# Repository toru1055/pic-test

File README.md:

# pic-test

## プッシュでラジオ体操
### 1. sin波で音楽再生
  - [x] オーディオアンプなし版
    - [x] 020 一定間隔でLEDを点滅させたい（MCCでタイマ設定）
    - [x] 075 MCCでオペアンプを設定して使いたい
    - [x] 101 正弦波を出力したい
  - [ ] オーディオアンプあり版

### 2. SPI通信でフラッシュメモリ読み書き
  - [x] 071 MCCでUSARTを設定して使いたい
    - [x] `$ screen /dev/tty.usbserial-0001 9600`
  - [x] 074 MCCでSPIを設定して使いたい
  - [x] 051 SPI接続の大容量フラッシュメモリを使いたい

### 3. フラッシュメモリから音声データを再生
  - [x] WAV形式のフォーマットを理解する
  - [x] `$ xxd 1164_8bit.wav | head`を見れば大体わかるが、データ部は80バイト目くらいからなので80バイトオフセットすれば良さそう
  - [x] [wav converter](https://audio.online-convert.com/convert-to-wav): 8bit モノラルの1000Hzに変換
  - [x] 104 WAVファイルをフラッシュメモリに書き込みたい
    - [x] windowsのteratermが最適。
  - [x] 103 WAVファイルの音楽を再生したい

### 4. ボタン割り込み制御：ボタンを押したら対応する音声ファイルを割り込み再生
- [x] Pin ManagerでIOC対象のPINを設定
- [x] Timer割り込みではなく、通常のDelayメソッドで音楽再生するメソッドを用意
- [x] Interrupt Handlerを実装して設定する
- [x] 1, 2番pinを押したら再生

### 5. 仕上げ
- [ ] ラジオ体操の音源を入れる
- [ ] PCBの設計

### 6. 音源をWAV形式で用意する
#### ffmpegをインストール
```
$ brew install homebrew-ffmpeg/ffmpeg/ffmpeg
```

#### mp3音源を連結する
```
$ for f in *.mp3; do echo "file '$f'" >> mylist.txt; done
$ ffmpeg -f concat -safe 0 -i mylist.txt -c copy output.mp3
```

#### MP3→WAV(8kHz,8bit,mono)へ変換
```
$ ffmpeg -i output.mp3 -ac 1 -ar 8000 -acodec pcm_u8 output.wav
```

## 音声ファイルのwifiアップロード
### 1. esp-wroom-02でアップロードされたファイルをSPI通信でフラッシュメモリ書き込み

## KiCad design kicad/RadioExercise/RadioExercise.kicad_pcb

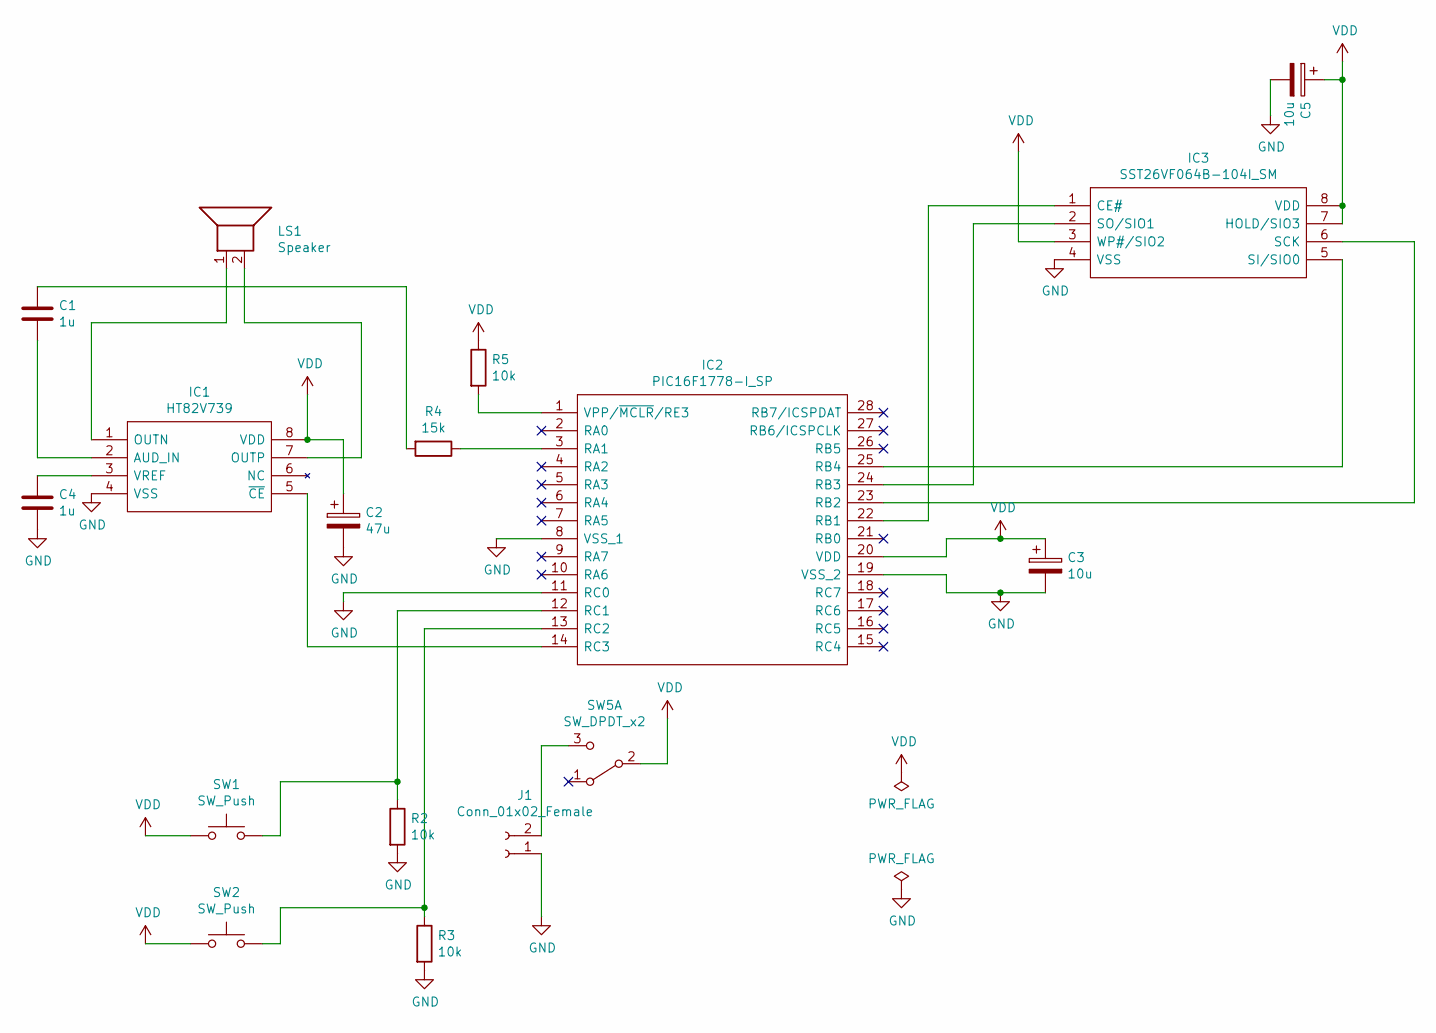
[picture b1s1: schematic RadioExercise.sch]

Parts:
C1, C4: 1u; C_Disc_D7.5mm_W5.0mm_P5.00mm
C2: 47u; CP_Radial_D4.0mm_P1.50mm
C3, C5: 10u; CP_Radial_D4.0mm_P1.50mm
IC1: HT82V739; DIP-8_W7.62mm; Manufacturer_Part_Number HT82V739
IC2: PIC16F1778-I_SP; DIP794W56P254L3486H508Q28N; Manufacturer_Part_Number PIC16F1778-I/SP; Mouser Part Number 579-PIC16F1778-I/SP
IC3: SST26VF064B-104I_SM; SOIC127P794X203-8N; Manufacturer_Part_Number SST26VF064B-104I/SM; Mouser Part Number 579-ST26VF064B104ISM
J1: Conn_01x02_Female; Conn_01x02_SMD
LS1: Speaker; Conn_01x02_SMD
R2, R3, R5: 10k; R_Axial_DIN0207_L6.3mm_D2.5mm_P7.62mm_Horizontal
R4: 15k; R_Axial_DIN0207_L6.3mm_D2.5mm_P7.62mm_Horizontal
SW1, SW2: SW_Push; SW_PUSH_6mm
SW5: SW_DPDT_x2; SW_slide_01x03_THT

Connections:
GND: C2.2, C3.2, C4.2, C5.2, IC1.4 (VSS), IC2.8 (VSS_1), IC2.11 (RC0), IC2.19 (VSS_2), IC3.4 (VSS), J1.1, R2.2, R3.2
unnamed: C1.1, R4.2
unnamed: C1.2, IC1.2 (AUD_IN)
unnamed: C4.1, IC1.3 (VREF)
unnamed: IC1.1 (OUTN), LS1.1
unnamed: IC1.5 (~CE), IC2.14 (RC3)
unnamed: IC1.7 (OUTP), LS1.2
unnamed: IC2.1 (VPP/~MCLR~/RE3), R5.2
unnamed: IC2.3 (RA1), R4.1
unnamed: IC2.12 (RC1), R2.1, SW1.2
unnamed: IC2.13 (RC2), R3.1, SW2.2
unnamed: IC2.22 (RB1), IC3.1 (CE#)
unnamed: IC2.23 (RB2), IC3.6 (SCK)
unnamed: IC2.24 (RB3), IC3.2 (SO/SIO1)
unnamed: IC2.25 (RB4), IC3.5 (SI/SIO0)
unnamed: J1.2, SW5.3 (C)
VDD: C2.1, C3.1, C5.1, IC1.8 (VDD), IC2.20 (VDD), IC3.3 (WP#/SIO2), IC3.7 (HOLD/SIO3), IC3.8 (VDD), R5.1, SW1.1, SW2.1, SW5.2 (B)

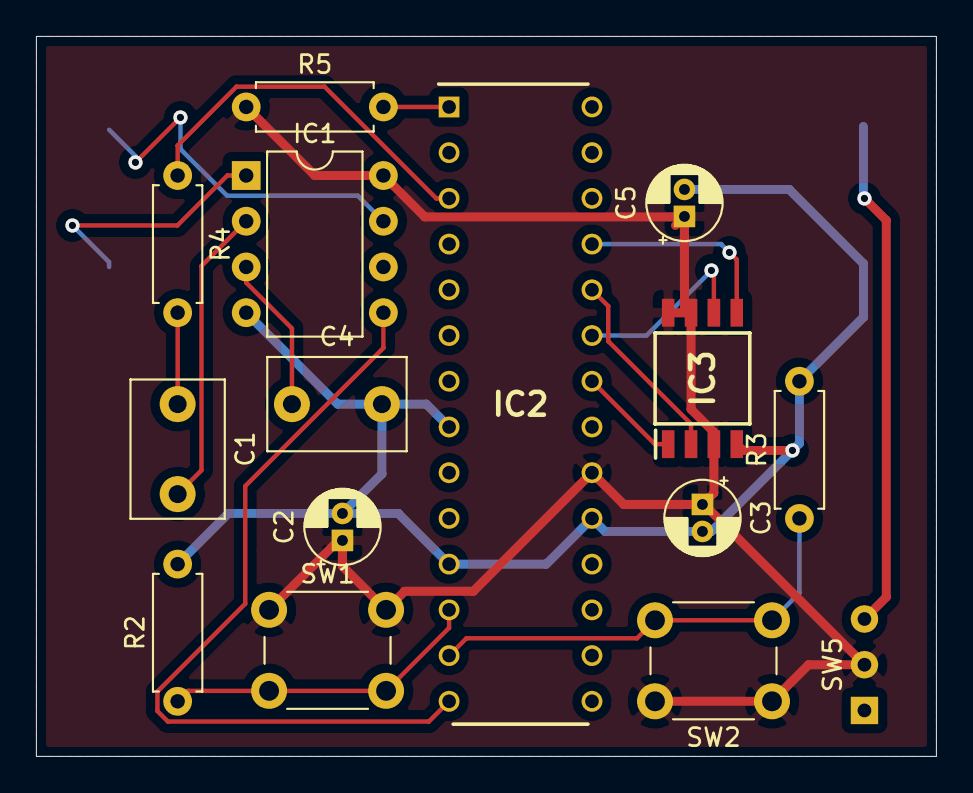
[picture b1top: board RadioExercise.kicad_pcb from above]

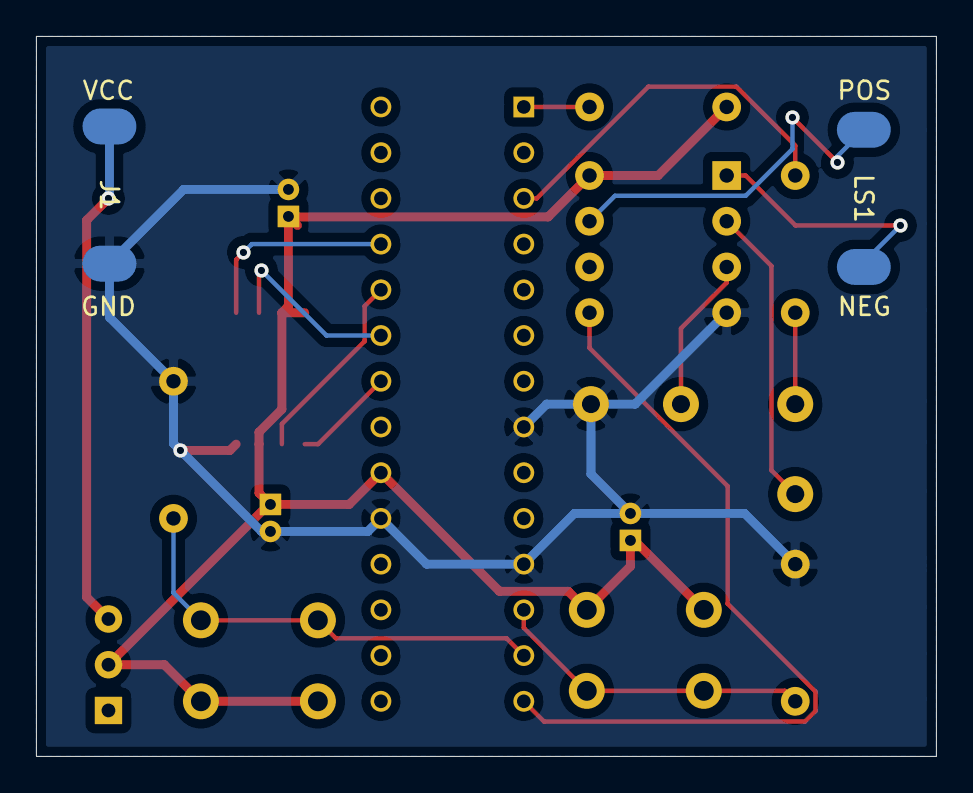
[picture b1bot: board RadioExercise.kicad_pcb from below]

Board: 2 copper layers, 50.0 x 40.0 mm, 17 parts (2 on the bottom side), 17 nets.

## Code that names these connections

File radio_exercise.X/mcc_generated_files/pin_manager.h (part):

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#define RA1_SetHigh()            do { LATAbits.LATA1 = 1; } while(0)
#define RA1_SetLow()             do { LATAbits.LATA1 = 0; } while(0)
#define RA1_Toggle()             do { LATAbits.LATA1 = ~LATAbits.LATA1; } while(0)
#define RA1_GetValue()              PORTAbits.RA1
#define RA1_SetDigitalInput()    do { TRISAbits.TRISA1 = 1; } while(0)
#define RA1_SetDigitalOutput()   do { TRISAbits.TRISA1 = 0; } while(0)
#define RA1_SetPullup()             do { WPUAbits.WPUA1 = 1; } while(0)
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// get/set IO_RB1 aliases
#define IO_RB1_TRIS                 TRISBbits.TRISB1
#define IO_RB1_LAT                  LATBbits.LATB1
#define IO_RB1_PORT                 PORTBbits.RB1
#define IO_RB1_WPU                  WPUBbits.WPUB1
#define IO_RB1_ANS                  ANSELBbits.ANSB1
#define IO_RB1_SetHigh()            do { LATBbits.LATB1 = 1; } while(0)
#define IO_RB1_SetLow()             do { LATBbits.LATB1 = 0; } while(0)
#define IO_RB1_Toggle()             do { LATBbits.LATB1 = ~LATBbits.LATB1; } while(0)
#define IO_RB1_GetValue()           PORTBbits.RB1
#define IO_RB1_SetDigitalInput()    do { TRISBbits.TRISB1 = 1; } while(0)
#define IO_RB1_SetDigitalOutput()   do { TRISBbits.TRISB1 = 0; } while(0)
#define IO_RB1_SetPullup()          do { WPUBbits.WPUB1 = 1; } while(0)
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#define RB2_SetHigh()            do { LATBbits.LATB2 = 1; } while(0)
#define RB2_SetLow()             do { LATBbits.LATB2 = 0; } while(0)
#define RB2_Toggle()             do { LATBbits.LATB2 = ~LATBbits.LATB2; } while(0)
#define RB2_GetValue()              PORTBbits.RB2
#define RB2_SetDigitalInput()    do { TRISBbits.TRISB2 = 1; } while(0)
#define RB2_SetDigitalOutput()   do { TRISBbits.TRISB2 = 0; } while(0)
#define RB2_SetPullup()             do { WPUBbits.WPUB2 = 1; } while(0)
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#define RB3_SetHigh()            do { LATBbits.LATB3 = 1; } while(0)
#define RB3_SetLow()             do { LATBbits.LATB3 = 0; } while(0)
#define RB3_Toggle()             do { LATBbits.LATB3 = ~LATBbits.LATB3; } while(0)
#define RB3_GetValue()              PORTBbits.RB3
#define RB3_SetDigitalInput()    do { TRISBbits.TRISB3 = 1; } while(0)
#define RB3_SetDigitalOutput()   do { TRISBbits.TRISB3 = 0; } while(0)
#define RB3_SetPullup()             do { WPUBbits.WPUB3 = 1; } while(0)
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#define RB4_SetHigh()            do { LATBbits.LATB4 = 1; } while(0)
#define RB4_SetLow()             do { LATBbits.LATB4 = 0; } while(0)
#define RB4_Toggle()             do { LATBbits.LATB4 = ~LATBbits.LATB4; } while(0)
#define RB4_GetValue()              PORTBbits.RB4
#define RB4_SetDigitalInput()    do { TRISBbits.TRISB4 = 1; } while(0)
#define RB4_SetDigitalOutput()   do { TRISBbits.TRISB4 = 0; } while(0)
#define RB4_SetPullup()             do { WPUBbits.WPUB4 = 1; } while(0)
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// get/set IO_RC0 aliases
#define IO_RC0_TRIS                 TRISCbits.TRISC0
#define IO_RC0_LAT                  LATCbits.LATC0
#define IO_RC0_PORT                 PORTCbits.RC0
#define IO_RC0_WPU                  WPUCbits.WPUC0
#define IO_RC0_OD                   ODCONCbits.ODC0
#define IO_RC0_SetHigh()            do { LATCbits.LATC0 = 1; } while(0)
#define IO_RC0_SetLow()             do { LATCbits.LATC0 = 0; } while(0)
#define IO_RC0_Toggle()             do { LATCbits.LATC0 = ~LATCbits.LATC0; } while(0)
#define IO_RC0_GetValue()           PORTCbits.RC0
#define IO_RC0_SetDigitalInput()    do { TRISCbits.TRISC0 = 1; } while(0)
#define IO_RC0_SetDigitalOutput()   do { TRISCbits.TRISC0 = 0; } while(0)
#define IO_RC0_SetPullup()          do { WPUCbits.WPUC0 = 1; } while(0)
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// get/set IO_RC1 aliases
#define IO_RC1_TRIS                 TRISCbits.TRISC1
#define IO_RC1_LAT                  LATCbits.LATC1
#define IO_RC1_PORT                 PORTCbits.RC1
#define IO_RC1_WPU                  WPUCbits.WPUC1
#define IO_RC1_OD                   ODCONCbits.ODC1
#define IO_RC1_SetHigh()            do { LATCbits.LATC1 = 1; } while(0)
#define IO_RC1_SetLow()             do { LATCbits.LATC1 = 0; } while(0)
#define IO_RC1_Toggle()             do { LATCbits.LATC1 = ~LATCbits.LATC1; } while(0)
#define IO_RC1_GetValue()           PORTCbits.RC1
#define IO_RC1_SetDigitalInput()    do { TRISCbits.TRISC1 = 1; } while(0)
#define IO_RC1_SetDigitalOutput()   do { TRISCbits.TRISC1 = 0; } while(0)
#define IO_RC1_SetPullup()          do { WPUCbits.WPUC1 = 1; } while(0)
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// get/set IO_RC2 aliases
#define IO_RC2_TRIS                 TRISCbits.TRISC2
#define IO_RC2_LAT                  LATCbits.LATC2
#define IO_RC2_PORT                 PORTCbits.RC2
#define IO_RC2_WPU                  WPUCbits.WPUC2
#define IO_RC2_OD                   ODCONCbits.ODC2
#define IO_RC2_ANS                  ANSELCbits.ANSC2
#define IO_RC2_SetHigh()            do { LATCbits.LATC2 = 1; } while(0)
#define IO_RC2_SetLow()             do { LATCbits.LATC2 = 0; } while(0)
#define IO_RC2_Toggle()             do { LATCbits.LATC2 = ~LATCbits.LATC2; } while(0)
#define IO_RC2_GetValue()           PORTCbits.RC2
#define IO_RC2_SetDigitalInput()    do { TRISCbits.TRISC2 = 1; } while(0)
#define IO_RC2_SetDigitalOutput()   do { TRISCbits.TRISC2 = 0; } while(0)
#define IO_RC2_SetPullup()          do { WPUCbits.WPUC2 = 1; } while(0)
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// get/set IO_RC3 aliases
#define IO_RC3_TRIS                 TRISCbits.TRISC3
#define IO_RC3_LAT                  LATCbits.LATC3
#define IO_RC3_PORT                 PORTCbits.RC3
#define IO_RC3_WPU                  WPUCbits.WPUC3
#define IO_RC3_OD                   ODCONCbits.ODC3
#define IO_RC3_ANS                  ANSELCbits.ANSC3
#define IO_RC3_SetHigh()            do { LATCbits.LATC3 = 1; } while(0)
#define IO_RC3_SetLow()             do { LATCbits.LATC3 = 0; } while(0)
#define IO_RC3_Toggle()             do { LATCbits.LATC3 = ~LATCbits.LATC3; } while(0)
#define IO_RC3_GetValue()           PORTCbits.RC3
#define IO_RC3_SetDigitalInput()    do { TRISCbits.TRISC3 = 1; } while(0)
#define IO_RC3_SetDigitalOutput()   do { TRISCbits.TRISC3 = 0; } while(0)
#define IO_RC3_SetPullup()          do { WPUCbits.WPUC3 = 1; } while(0)
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
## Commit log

2021-03-22 mod sin wave
2021-03-22 add README
2021-03-23 mod settings
2021-03-24 fix sin_wave
2021-03-24 change README
2021-03-29 add usart_test1
2021-03-30 make eusart_test2
2021-03-30 fix eusart_test2
2021-03-30 mod readme
2021-03-30 add link
2021-03-30 change
2021-04-03 create spi_flash pj
2021-04-03 add spi methods
2021-04-03 flash read write
2021-04-03 create radio exercise project
2021-04-03 add DAC1 and OPA1
2021-04-03 add TMR2
2021-04-03 add EUSART
2021-04-03 add MSSP
2021-04-03 set pin_manager
2021-04-03 implement main.c
2021-04-06 add status lamp
2021-04-06 add debuger
2021-04-07 wakaran
2021-04-07 dekita
2021-04-07 change save music
2021-04-08 debug
2021-04-08 change tmr and eusart settings
2021-04-09 change settings
2021-04-09 memo
2021-04-09 割り込みで音源再生するように修正
2021-04-10 ボタン制御可能に
2021-04-10 add memory but not working
2021-04-10 割り込み
2021-04-11 内蔵フラッシュメモリに保存できるようにした1
2021-04-11 オーディオアンプのON/OFF制御
2021-04-12 オーディオアンプを待機中OFFに
2021-04-12 change var
2021-04-13 add kicad dir
2021-04-15 SPIフラッシュに曲設定を保存するように変更
2021-04-15 update1
2021-04-15 remove wire
2021-04-15 wire
2021-04-15 add 2x2
2021-04-16 add music_writer
2021-04-27 配線が繋がってなかったので修正

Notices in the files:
radio_exercise.X/mcc_generated_files/pin_manager.h:
(c) 2018 Microchip Technology Inc. and its subsidiaries.
